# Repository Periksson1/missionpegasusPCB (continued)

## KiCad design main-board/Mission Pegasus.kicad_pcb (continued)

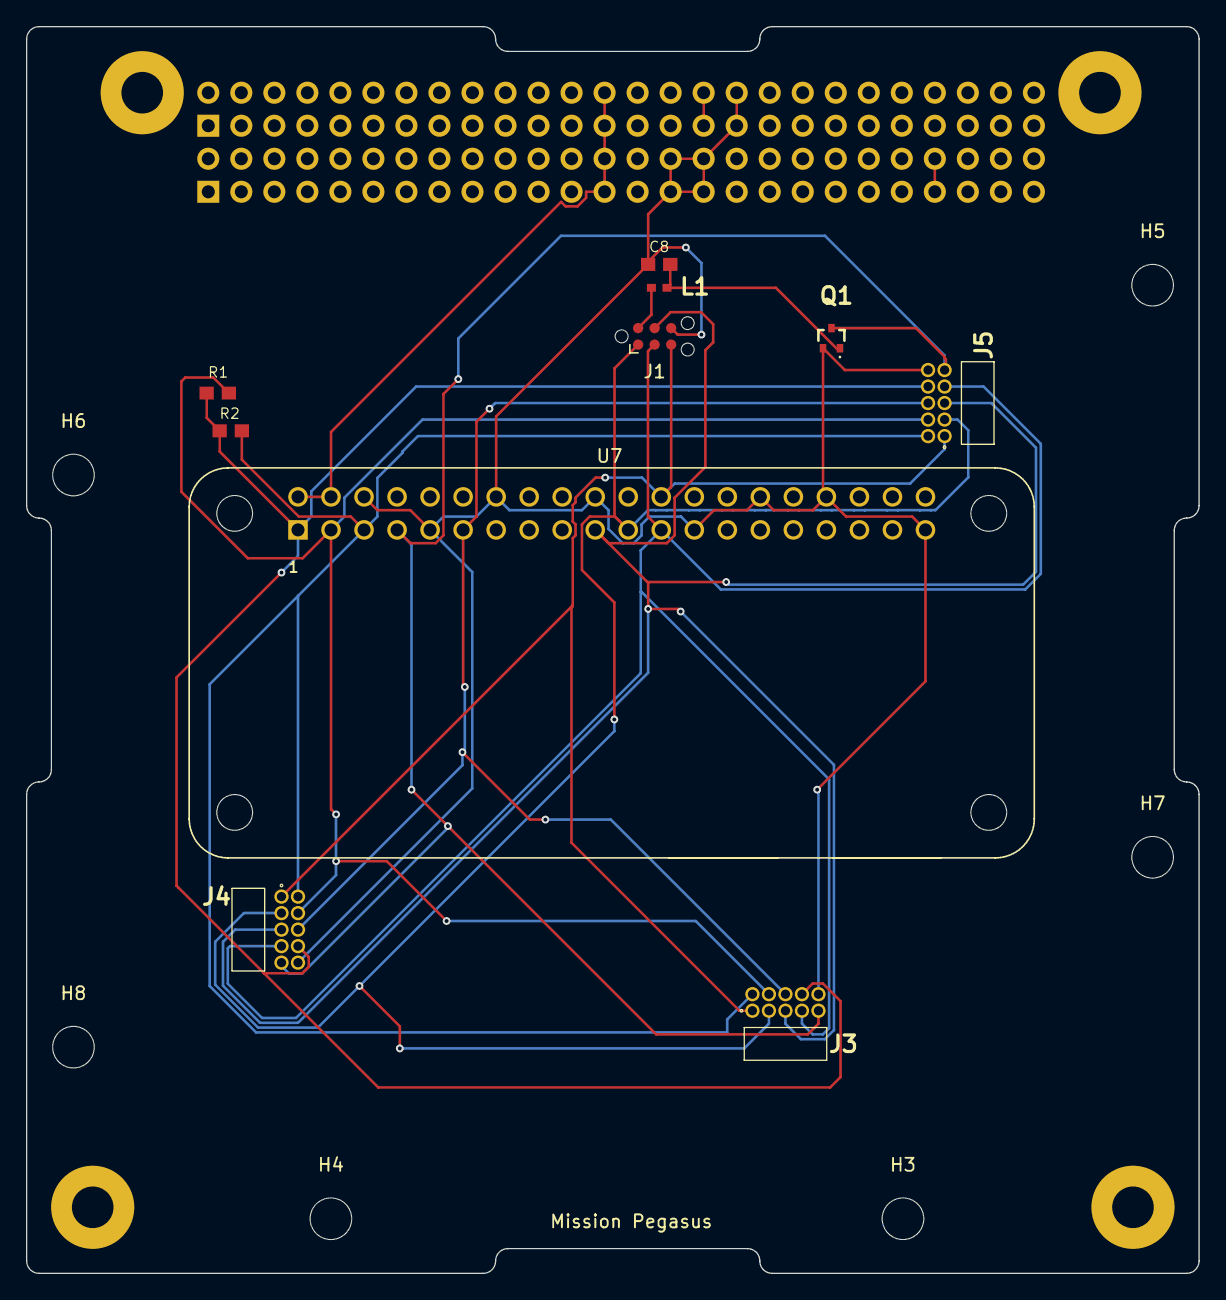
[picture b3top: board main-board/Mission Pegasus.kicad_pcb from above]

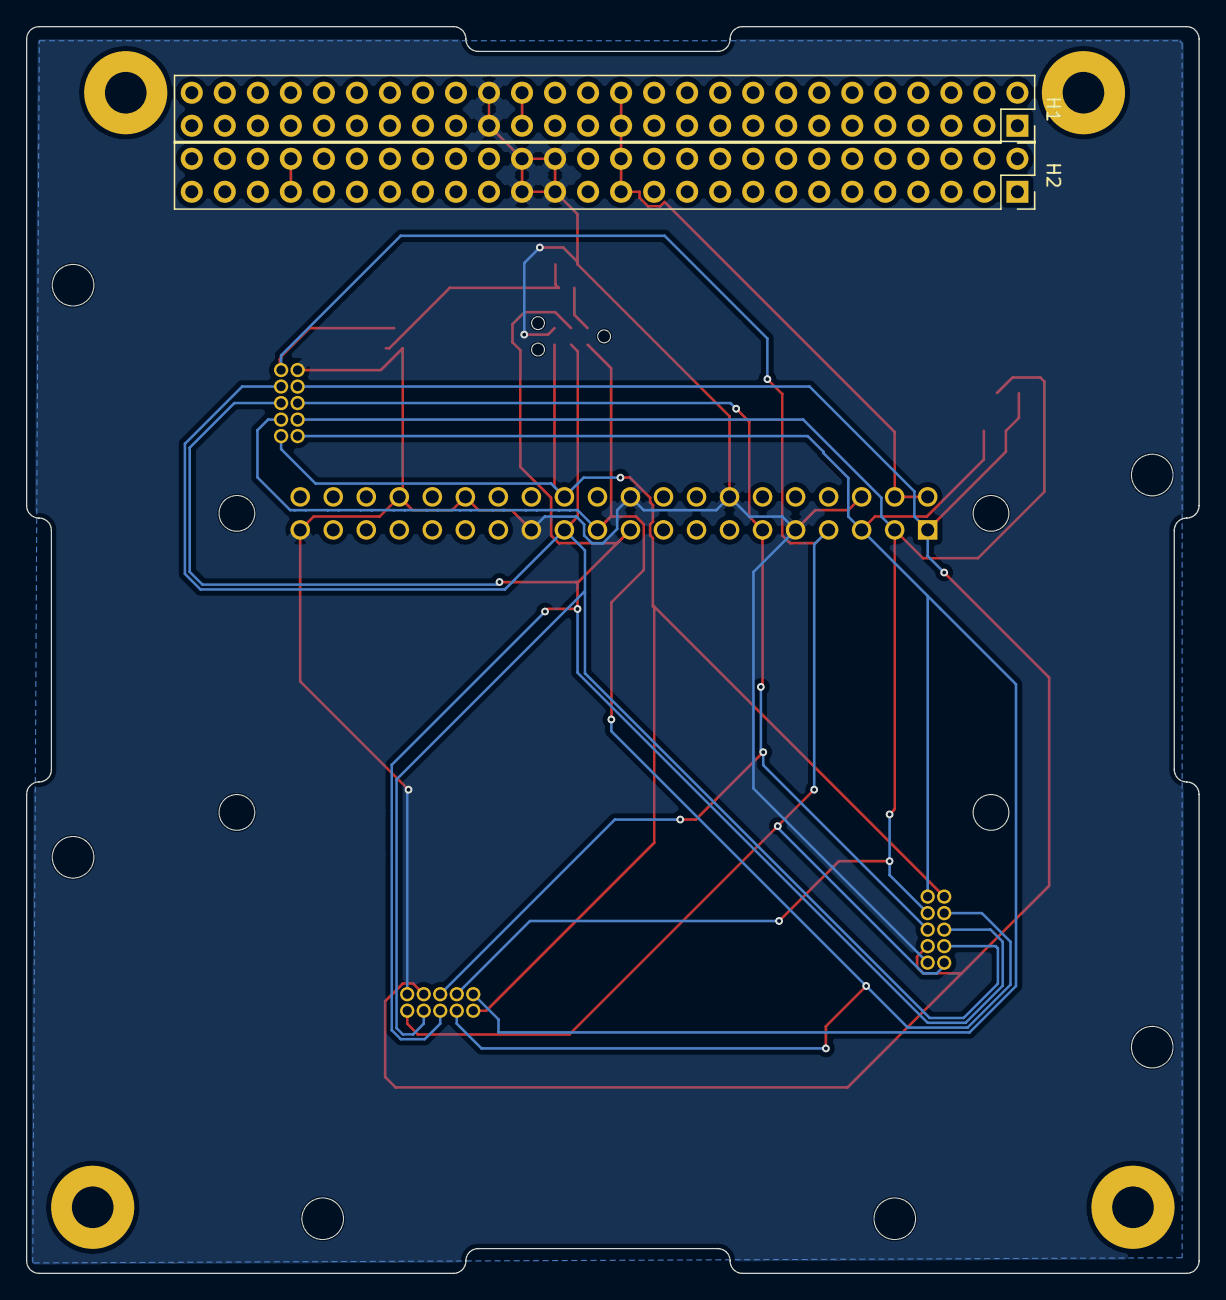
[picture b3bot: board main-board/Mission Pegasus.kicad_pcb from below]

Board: 2 copper layers, 90.2 x 95.9 mm, 22 parts (2 on the bottom side), 15 nets.

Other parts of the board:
M1, M2, M3, M4: MountingHole; MountingHole_3.2mm_M3_Pad

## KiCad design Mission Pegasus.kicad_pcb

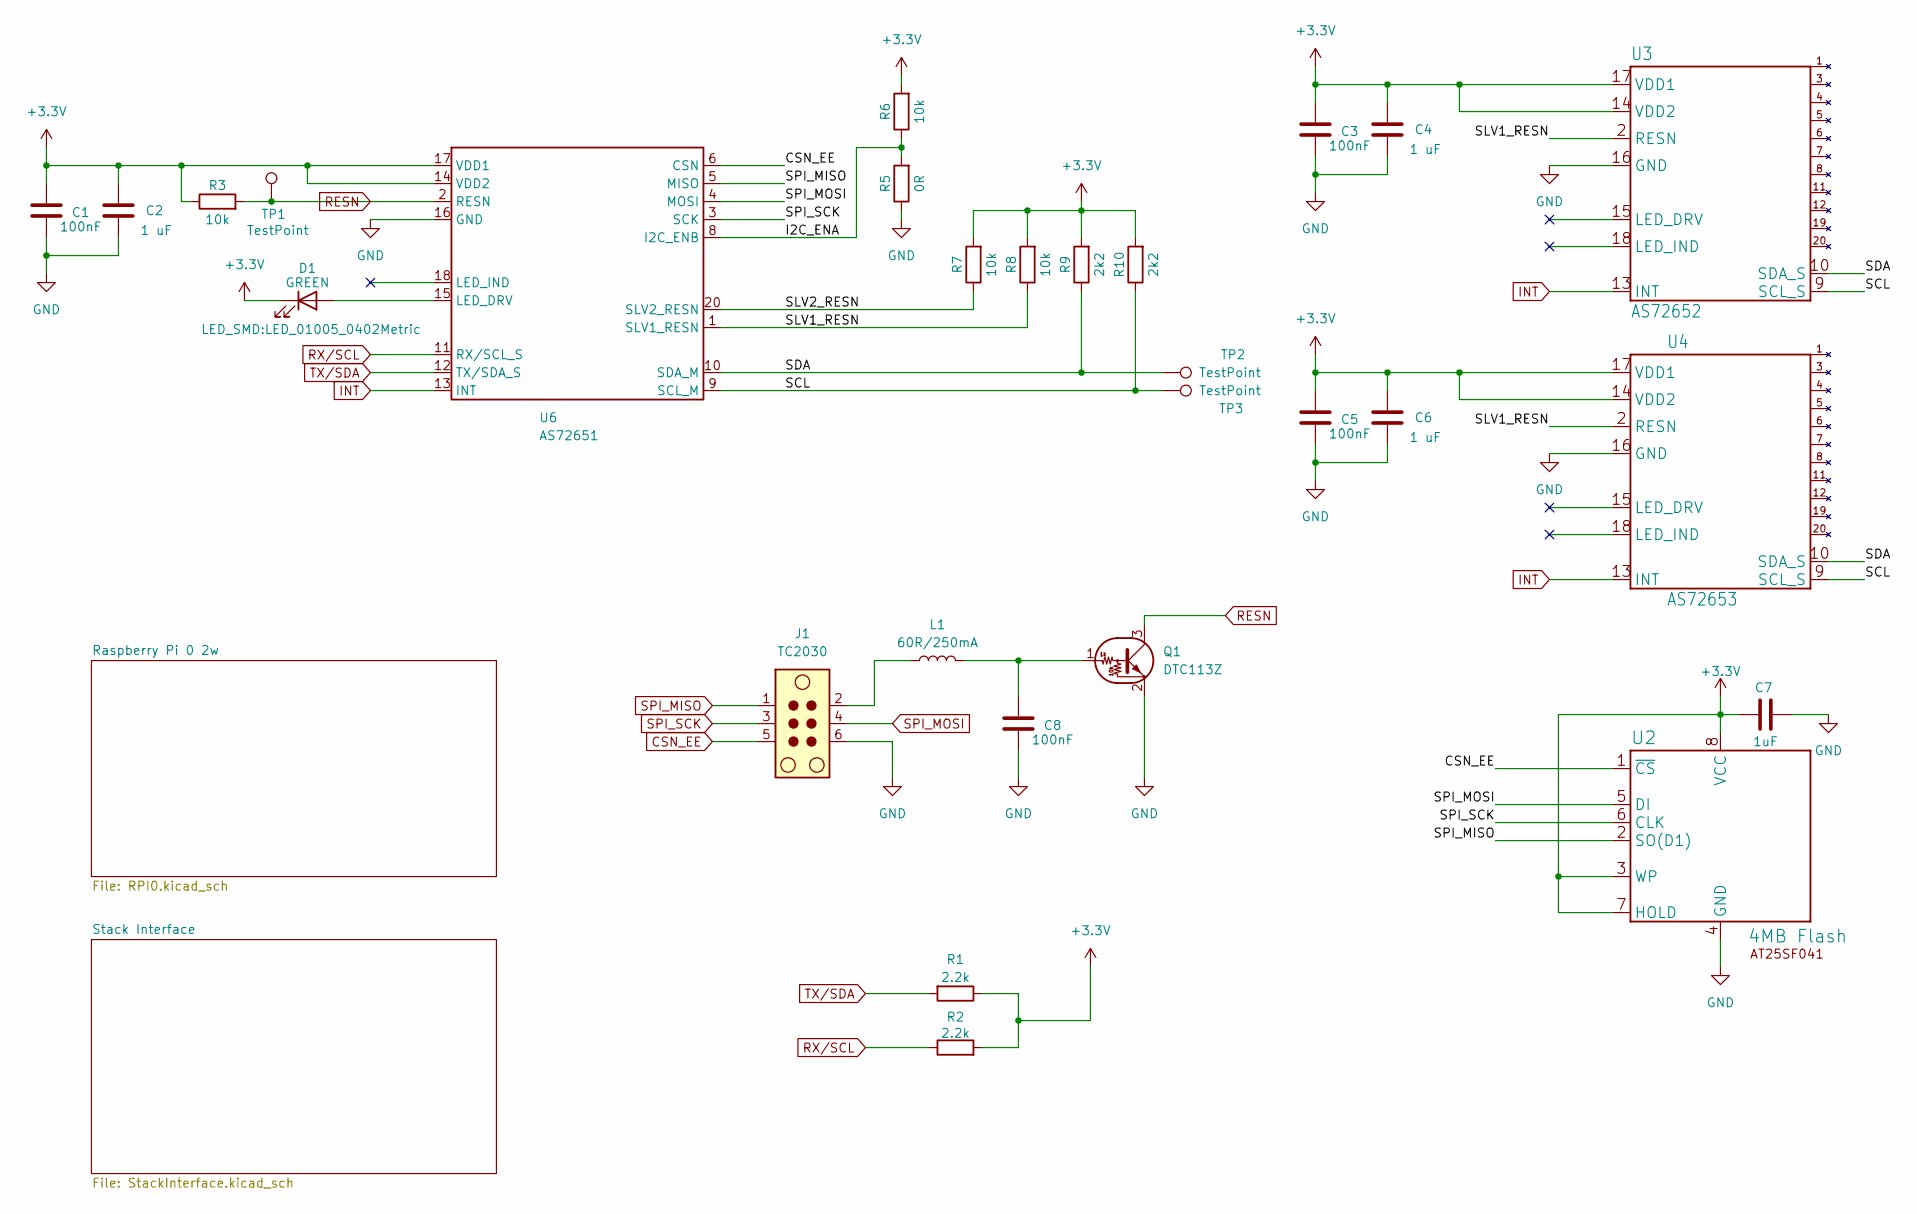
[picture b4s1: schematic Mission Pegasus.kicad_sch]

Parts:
C1, C3, C5, C8: 100nF; 0603
C2, C4, C6: 1 uF; 0603
C7: 1uF; 0603
D1: GREEN; LED_01005_0402Metric
J1: TC2030; Tag-Connect_TC2030-IDC-NL_2x03_P1.27mm_Vertical
L1: 60R/250mA; 0402
Q1: DTC113Z; DTC113ZUA
R1, R2: 2.2k; 0603
R3, R6, R7, R8: 10k; 0603
R5: 0R; 0603
R9, R10: 2k2; 0603
TP1, TP2, TP3: TestPoint; TestPoint_Pad_D1.0mm
U2: 4MB Flash; 4MbFlash
U3: AS72652; AS72651
U4: AS72653; AS72651
U6: AS72651; AMS_LGA-20_4.7x4.5mm_P0.65mm

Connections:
+3.3V: C1.1, C2.1, C3.1, C4.1, C5.1, C6.1, C7.1, D1.1 (K), R1.1, R2.2, R3.1, R6.2, R7.2, R8.2, R9.2, R10.2, U2.3 (WP), U2.7 (HOLD), U2.8 (VCC), U3.14 (VDD2), U3.17 (VDD1), U4.14 (VDD2), U4.17 (VDD1), U6.14 (VDD2), U6.17 (VDD1); also elsewhere on the board
/I2C_ENA: R5.2, R6.1, U6.8 (I2C_ENB)
/SCL: R10.1, TP3.1 (1_1), U3.9 (SCL_S), U4.9 (SCL_S), U6.9 (SCL_M)
/SDA: R9.1, TP2.1 (1_1), U3.10 (SDA_S), U4.10 (SDA_S), U6.10 (SDA_M)
/SLV1_RESN: R8.1, U3.2 (RESN), U4.2 (RESN), U6.1 (SLV1_RESN)
/SLV2_RESN: R7.1, U6.20 (SLV2_RESN)
CSN_EE: J1.5, U2.1 (~CS), U6.6 (CSN); also elsewhere on the board
GND: C1.2, C2.2, C3.2, C4.2, C5.2, C6.2, C7.2, C8.2, J1.6, Q1.2 (E), R5.1, U2.4 (GND), U3.16 (GND), U4.16 (GND), U6.16 (GND); also elsewhere on the board
INT: U3.13 (INT), U4.13 (INT), U6.13 (INT); also elsewhere on the board
unnamed: D1.2 (A), U6.15 (LED_DRV)
unnamed: J1.2, L1.1
unnamed: C8.1, L1.2, Q1.1 (B)
RESN: Q1.3 (C), R3.2, TP1.1 (1_1), U6.2 (RESN); also elsewhere on the board
RX/SCL: R2.1, U6.11 (RX/SCL_S); also elsewhere on the board
SPI_MISO: J1.1, U2.2 (SO(D1)), U6.5 (MISO); also elsewhere on the board
SPI_MOSI: J1.4, U2.5 (DI), U6.4 (MOSI); also elsewhere on the board
SPI_SCK: J1.3, U2.6 (CLK), U6.3 (SCK); also elsewhere on the board
TX/SDA: R1.2, U6.12 (TX/SDA_S); also elsewhere on the board

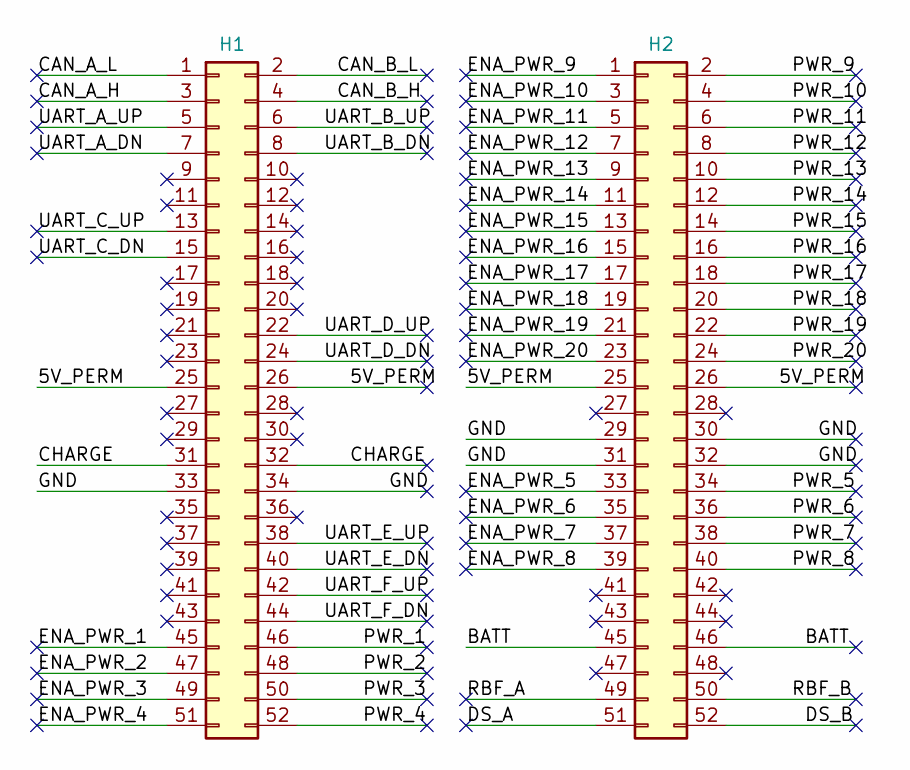
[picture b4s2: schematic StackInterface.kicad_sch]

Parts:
H1, H2: PC/104 Connector; PinSocket_2x26_P2.54mm_Vertical

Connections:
/Stack Interface/5V_PERM: H1.25, H1.26, H2.25, H2.26
/Stack Interface/BATT: H2.45, H2.46
/Stack Interface/CAN_A_H: H1.3
/Stack Interface/CAN_A_L: H1.1
/Stack Interface/CAN_B_H: H1.4
/Stack Interface/CAN_B_L: H1.2
/Stack Interface/CHARGE: H1.31, H1.32
/Stack Interface/DS_A: H2.51
/Stack Interface/DS_B: H2.52
/Stack Interface/ENA_PWR_1: H1.45
/Stack Interface/ENA_PWR_2: H1.47
/Stack Interface/ENA_PWR_3: H1.49
/Stack Interface/ENA_PWR_4: H1.51
/Stack Interface/ENA_PWR_5: H2.33
/Stack Interface/ENA_PWR_6: H2.35
/Stack Interface/ENA_PWR_7: H2.37
/Stack Interface/ENA_PWR_8: H2.39
/Stack Interface/ENA_PWR_9: H2.1
/Stack Interface/ENA_PWR_10: H2.3
/Stack Interface/ENA_PWR_11: H2.5
/Stack Interface/ENA_PWR_12: H2.7
/Stack Interface/ENA_PWR_13: H2.9
/Stack Interface/ENA_PWR_14: H2.11
/Stack Interface/ENA_PWR_15: H2.13
/Stack Interface/ENA_PWR_16: H2.15
/Stack Interface/ENA_PWR_17: H2.17
/Stack Interface/ENA_PWR_18: H2.19
/Stack Interface/ENA_PWR_19: H2.21
/Stack Interface/ENA_PWR_20: H2.23
/Stack Interface/GND: H1.33, H1.34, H2.29, H2.30, H2.31, H2.32
/Stack Interface/PWR_1: H1.46
/Stack Interface/PWR_2: H1.48
/Stack Interface/PWR_3: H1.50
/Stack Interface/PWR_4: H1.52
/Stack Interface/PWR_5: H2.34
/Stack Interface/PWR_6: H2.36
/Stack Interface/PWR_7: H2.38
/Stack Interface/PWR_8: H2.40
/Stack Interface/PWR_9: H2.2
/Stack Interface/PWR_10: H2.4
/Stack Interface/PWR_11: H2.6
/Stack Interface/PWR_12: H2.8
/Stack Interface/PWR_13: H2.10
/Stack Interface/PWR_14: H2.12
/Stack Interface/PWR_15: H2.14
/Stack Interface/PWR_16: H2.16
/Stack Interface/PWR_17: H2.18
/Stack Interface/PWR_18: H2.20
/Stack Interface/PWR_19: H2.22
/Stack Interface/PWR_20: H2.24
/Stack Interface/RBF_A: H2.49
/Stack Interface/RBF_B: H2.50
/Stack Interface/UART_A_DN: H1.7
/Stack Interface/UART_A_UP: H1.5
/Stack Interface/UART_B_DN: H1.8
/Stack Interface/UART_B_UP: H1.6
/Stack Interface/UART_C_DN: H1.15
/Stack Interface/UART_C_UP: H1.13
/Stack Interface/UART_D_DN: H1.24
/Stack Interface/UART_D_UP: H1.22
/Stack Interface/UART_E_DN: H1.40
/Stack Interface/UART_E_UP: H1.38
/Stack Interface/UART_F_DN: H1.44
/Stack Interface/UART_F_UP: H1.42

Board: 2 copper layers, 35 parts (2 on the bottom side), 22 nets, no tracks yet.

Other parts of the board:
M1, M2, M3, M4: MountingHole; MountingHole_3.2mm_M3_Pad
U7: RASPBERRY_PI_ZERO_2_W; RASPBERRYPI-ZERO_RPI-ZERO

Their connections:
+3.3V: U7.1 (3V3_1); also elsewhere on the board
CSN_EE: U7.24 (GPIO8/SPI_~CE0); also elsewhere on the board
GND: U7.6 (GND_6), U7.9 (GND_9), U7.14 (GND_14), U7.20 (GND_20), U7.25 (GND_25), U7.30 (GND_30), U7.34 (GND_34), U7.39 (GND_39); also elsewhere on the board
INT: U7.11 (GPIO17/GPIO_GEN0); also elsewhere on the board
RESN: U7.7 (GPIO4/GPIO_GCLK); also elsewhere on the board
RX/SCL: U7.5 (GPIO3/SCL); also elsewhere on the board
SPI_MISO: U7.21 (GPIO9/SPI_MISO); also elsewhere on the board
SPI_MOSI: U7.19 (GPIO10/SPI_MOSI); also elsewhere on the board
SPI_SCK: U7.23 (GPIO11/SPI_SCLK); also elsewhere on the board
TX/SDA: U7.3 (GPIO2/SDA1); also elsewhere on the board

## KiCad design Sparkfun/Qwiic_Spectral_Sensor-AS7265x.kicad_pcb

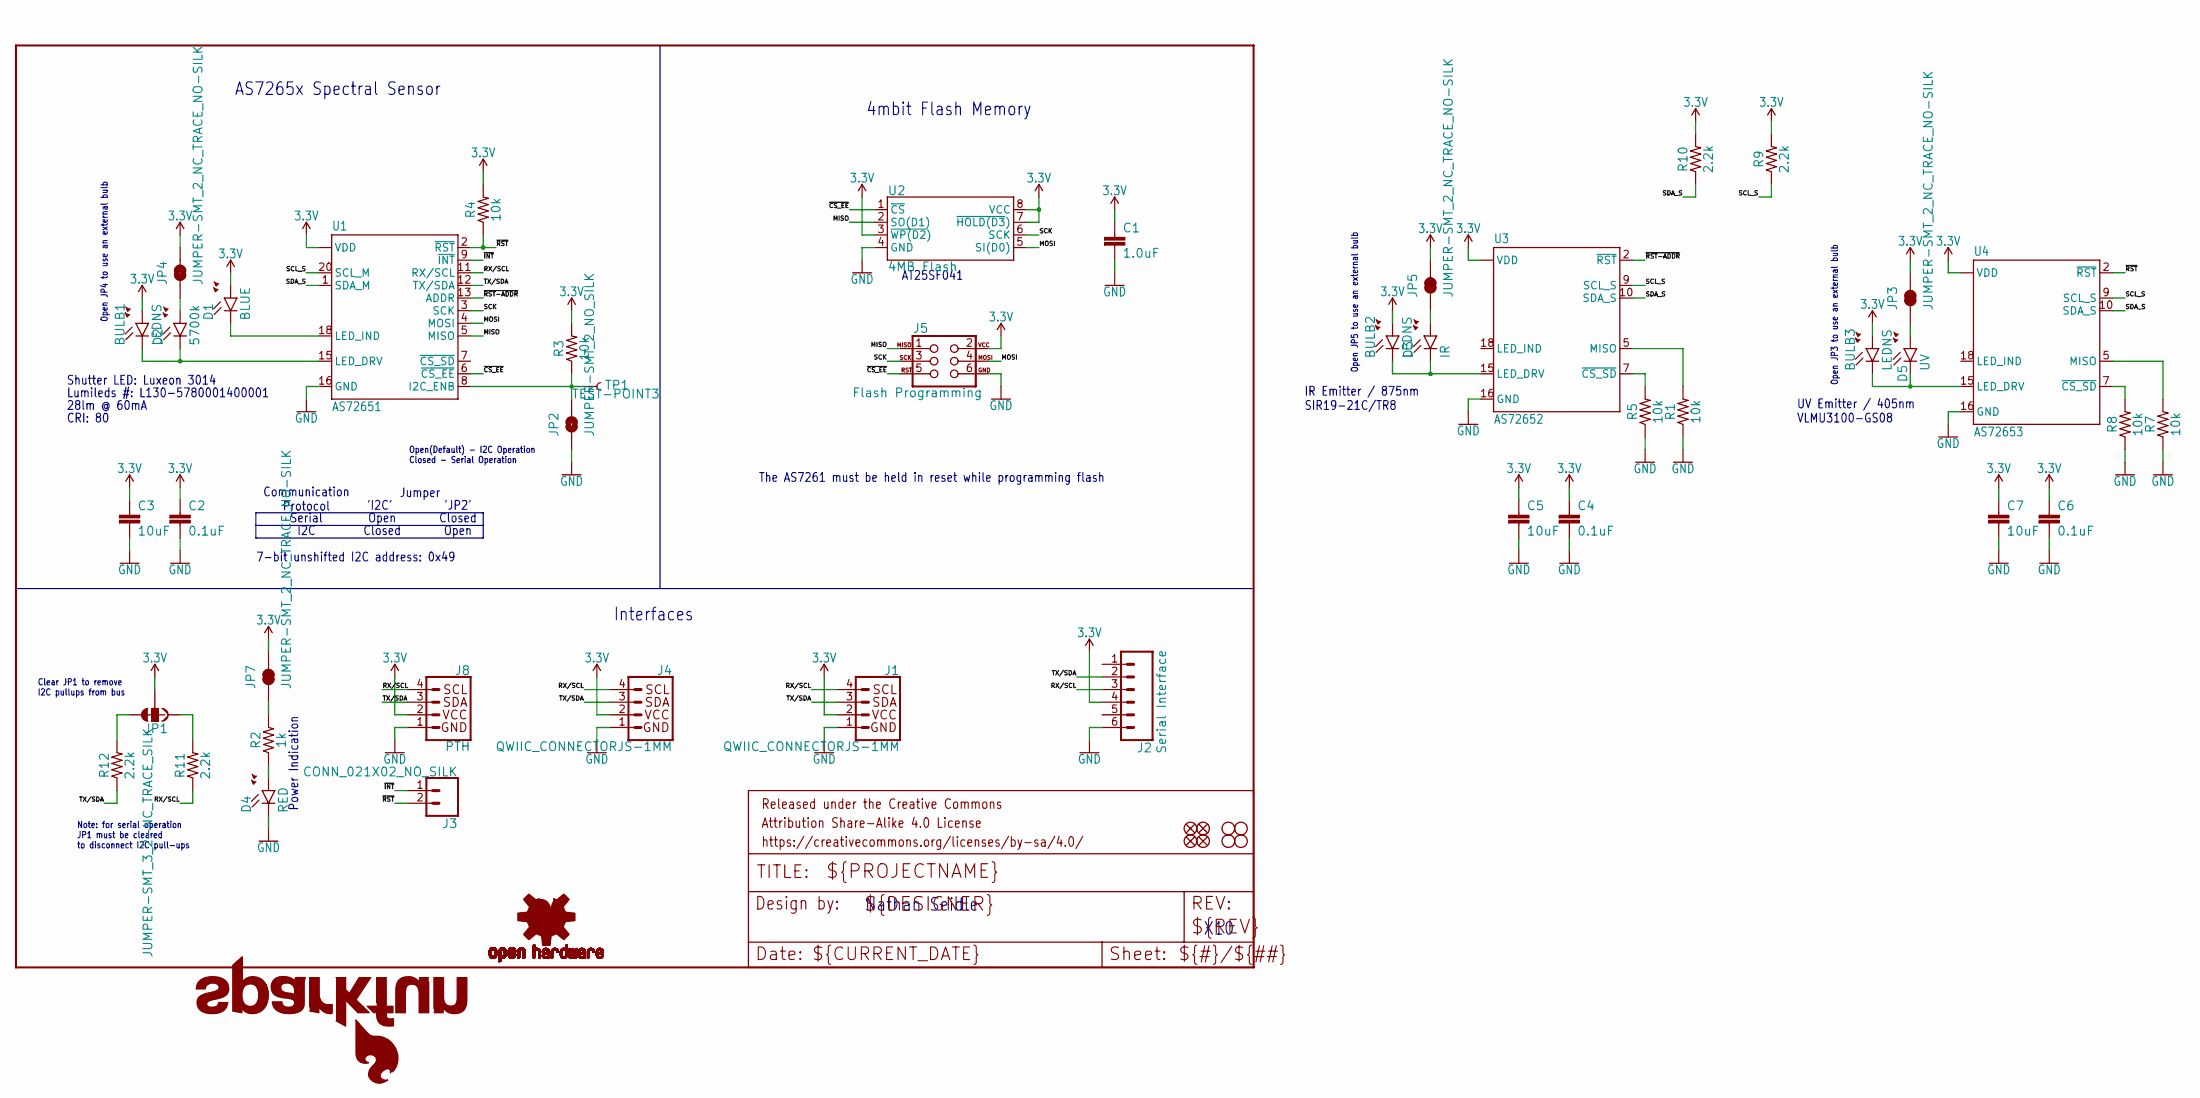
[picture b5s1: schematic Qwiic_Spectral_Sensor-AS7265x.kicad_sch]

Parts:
BULB1, BULB2, BULB3: LEDNS; LED_5MM_NOSILK
C1: 1.0uF; 0603
C2, C4, C6: 0.1uF; 0603
C3, C5, C7: 10uF; 0603
D1: BLUE; LED-0603
D2: 5700k; SUPER_BRIGHT_SMD_LED_3014
D3: IR; LED-0603
D4: RED; LED-0603
D5: UV; PLCC-2
FD1, FD2, FD3, FD4: FIDUCIAL1X2; FIDUCIAL-1X2
FRAME1: FRAME-LETTER; CREATIVE_COMMONS
H1, H2, H3, H4: STAND-OFF
J1, J4: QWIIC_CONNECTORJS-1MM; 1X04_1MM_RA
J2: Serial Interface; 1X06_NO_SILK
J3: CONN_021X02_NO_SILK; 1X02_NO_SILK
J5: Flash Programming; 2X3_TEST_POINTS
J8: PTH; 1X04_NO_SILK
JP1: JUMPER-SMT_3_2-NC_TRACE_SILK; SMT-JUMPER_3_2-NC_TRACE_SILK
JP2: JUMPER-SMT_2_NO_SILK; SMT-JUMPER_2_NO_SILK
JP3, JP4, JP5, JP7: JUMPER-SMT_2_NC_TRACE_NO-SILK; SMT-JUMPER_2_NC_TRACE_NO-SILK
LOGO1: SFE_LOGO_NAME_FLAME.1_INCH; SFE_LOGO_NAME_FLAME_.1
LOGO4: OSHW-LOGOS; OSHW-LOGO-S
R1, R3, R4, R5, R7, R8: 10k; 0603
R2: 1k; 0603
R9, R10, R11, R12: 2.2k; 0603
TP1: TEST-POINT3; PAD.03X.03
U1: AS72651; LGA20
U2: 4MB Flash; SO08
U3: AS72652; LGA20
U4: AS72653; LGA20

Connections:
3.3V: BULB1.A, BULB2.A, BULB3.A, C1.1, C2.1, C3.1, C4.1, C5.1, C6.1, C7.1, D1.A, J1.2, J2.4, J4.2, J5.2, J8.2, JP1.2, JP3.2, JP4.2, JP5.2, JP7.2, R3.2, R4.2, R9.2, R10.2, U1.14 (VDD), U1.17 (VDD), U2.3 (~WP(D2)), U2.7 (~HOLD(D3)), U2.8 (VCC), U3.14 (VDD), U3.17 (VDD), U4.14 (VDD), U4.17 (VDD)
GND: C1.2, C2.2, C3.2, C4.2, C5.2, C6.2, C7.2, D4.C, J1.1, J2.6, J4.1, J5.6, J8.1, JP2.1, R1.1, R5.1, R7.1, R8.1, U1.16 (GND), U2.4 (GND), U3.16 (GND), U4.16 (GND)
I2C_ENB: JP2.2, R3.1, TP1.P$1, U1.8 (I2C_ENB)
LED_DRV: BULB1.K (C), D2.C, U1.15 (LED_DRV)
LED_DRV1: BULB2.K (C), D3.C, U3.15 (LED_DRV)
LED_DRV2: BULB3.K (C), D5.C, U4.15 (LED_DRV)
MISO: J5.1, U1.5 (MISO), U2.2 (SO(D1))
MOSI: J5.4, U1.4 (MOSI), U2.5 (SI(D0))
unnamed: JP7.1, R2.2
unnamed: D1.C, U1.18 (LED_IND)
unnamed: R5.2, U3.7 (~CS_SD)
unnamed: JP1.3, R12.2
unnamed: JP1.1, R11.2
unnamed: D2.A, JP4.1
unnamed: D4.A, R2.1
unnamed: D3.A, JP5.1
unnamed: R1.2, U3.5 (MISO)
unnamed: D5.A, JP3.1
unnamed: R8.2, U4.7 (~CS_SD)
unnamed: R7.2, U4.5 (MISO)
RX/SCL: J1.4, J2.3, J4.4, J8.4, R11.1, U1.11 (RX/SCL)
SCK: J5.3, U1.3 (SCK), U2.6 (SCK)
SCL_S: R9.1, U1.20 (SCL_M), U3.9 (SCL_S), U4.9 (SCL_S)
SDA_S: R10.1, U1.1 (SDA_M), U3.10 (SDA_S), U4.10 (SDA_S)
TX/SDA: J1.3, J2.2, J4.3, J8.3, R12.1, U1.12 (TX/SDA)
~CS_EE: J5.5, U1.6 (~CS_EE), U2.1 (~CS)
~INT: J3.1, U1.9 (~INT)
~RST-ADDR: U1.13 (ADDR), U3.2 (~RST)
~RST: J3.2, R4.1, U1.2 (~RST), U4.2 (~RST)

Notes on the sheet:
28lm @ 60mA
Serial
Open JP5 to use an external bulb
4mbit Flash Memory
'JP2'
AT25SF041
Open
Lumileds #: L130-5780001400001
Open JP3 to use an external bulb
The AS7261 must be held in reset while programming flash
X10
IR Emitter / 875nm SIR19-21C/TR8
AS7265x Spectral Sensor
Nathan Seidle
Jumper
Power Indication
Note: for serial operation JP1 must be cleared to disconnect I2C pull-ups
Open JP4 to use an external bulb
Closed
Interfaces
Communication Protocol
Open(Default) - I2C Operation Closed - Serial Operation
'I2C'
Clear JP1 to remove I2C pullups from bus
CRI: 80
7-bit unshifted I2C address: 0x49
UV Emitter / 405nm VLMU3100-GS08
Shutter LED: Luxeon 3014
I2C

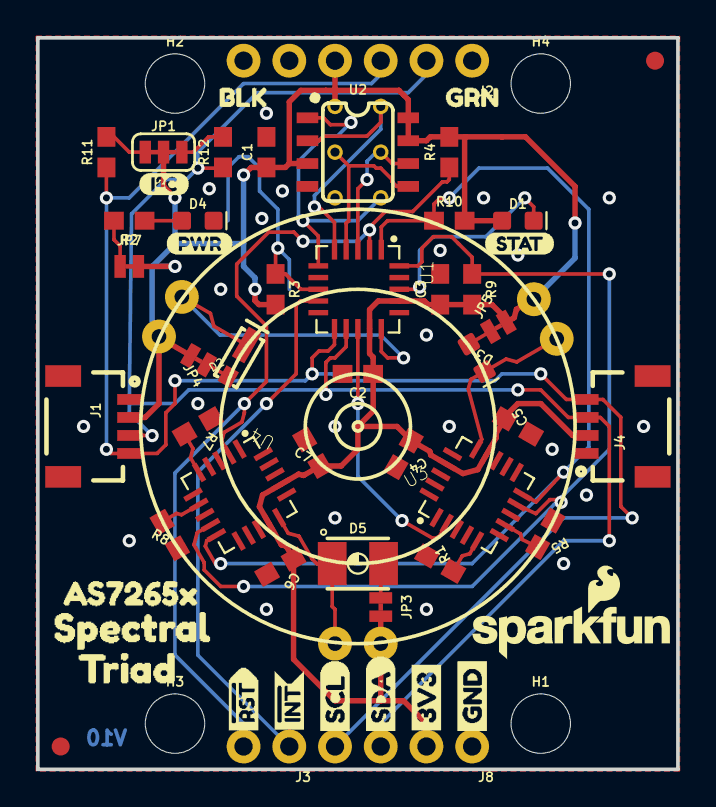
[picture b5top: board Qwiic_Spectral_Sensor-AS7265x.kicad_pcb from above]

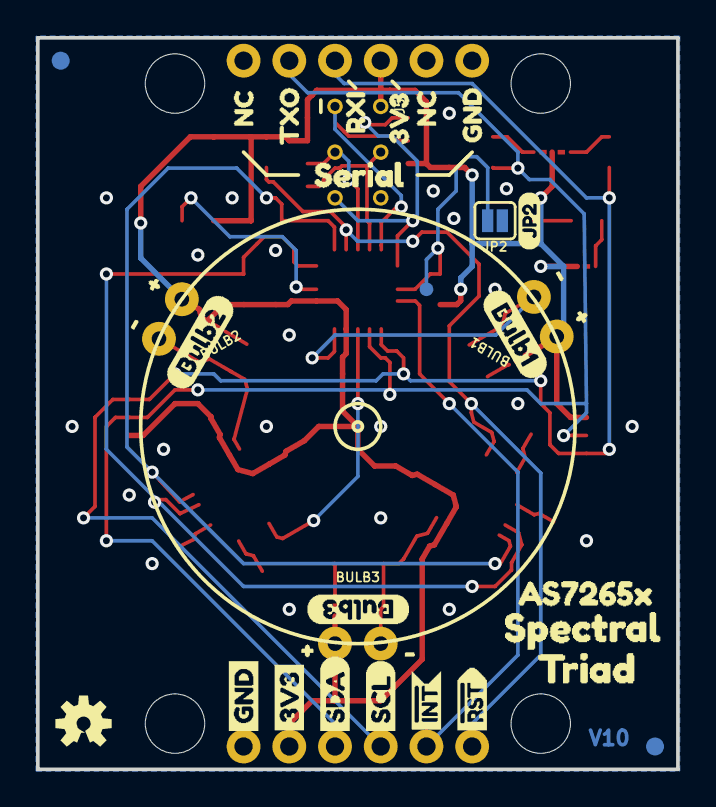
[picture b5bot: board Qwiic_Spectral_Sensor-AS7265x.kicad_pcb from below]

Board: 2 copper layers, 35.6 x 40.6 mm, 94 parts (35 on the bottom side), 29 nets.

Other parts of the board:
U$1, U$36, U$37: #0
U$2: I_SUPER2_C-()-03
U$3: PWR-()-03
U$4, U$14: AS7265X0
U$5: BULB15
U$6: BULB26
U$7: BULB37
U$8: JP20
U$9, U$13: SPECTRAL1
U$10: STAT4
U$11, U$12: TRIAD2
U$15: 3V33
U$16: BLK7
U$17: GND5
U$18: GRN6
U$19, U$20: NC4
U$21: RXI2
U$22: SERIAL0
U$23: TXO1
U$24, U$31: 3V3-04
U$25, U$30: GND-04
U$26, U$32: SDA-[)
U$27, U$33: SCL-[)
U$28, U$34: INT#-[_-04
U$29, U$35: RST#-[_-04
U$38, U$39, U$40: #1
